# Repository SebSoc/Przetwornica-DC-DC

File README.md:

# Przetwornica-DC-DC
Do budowy przetwornicy zastosowano specjalizowany sterownik MC34063. W tym układzie znajduje się generator impulsów o regulowanym współczynniku wypełnienia, komparator, źródło napięcia odniesienia z kompensacją temperaturową i stopień mocy z kontrolą prądu. Układ składa się z dwóch konfiguracji: przetwornica podwyższająca napięcie - step-up converter oraz przetwornica dostarczająca napięcia ujemne względem napięcia zasilającego - voltage inverting converter. Dzięki zastosowaniu tych dwóch konfiguracji można uzyskać napięcie symetryczne na wyjściu. Kondensatory C1 i C5 filtrują napięcie zasilania, rezystory R1 i R2 oraz analogicznie R5 i R6 połączone równolegle mają wypadkową oporność 0,5 Ω i są wykorzystywane jako obwód kontroli prądu. Kondensatory C3, C4 i dławik L2 oraz analogicznie C7, C8 i L4 filtrują napięcie wyjściowe, potencjometry R4 i R7 umożliwiają regulację tego napięcia. Pojemność C2 i C6 ustalają częstotliwość pracy. Elementy L1, D1 oraz L3, D2 są niezbędne do działania przetwornicy i to od nich głównie zależy jaką funkcję pełni układ.

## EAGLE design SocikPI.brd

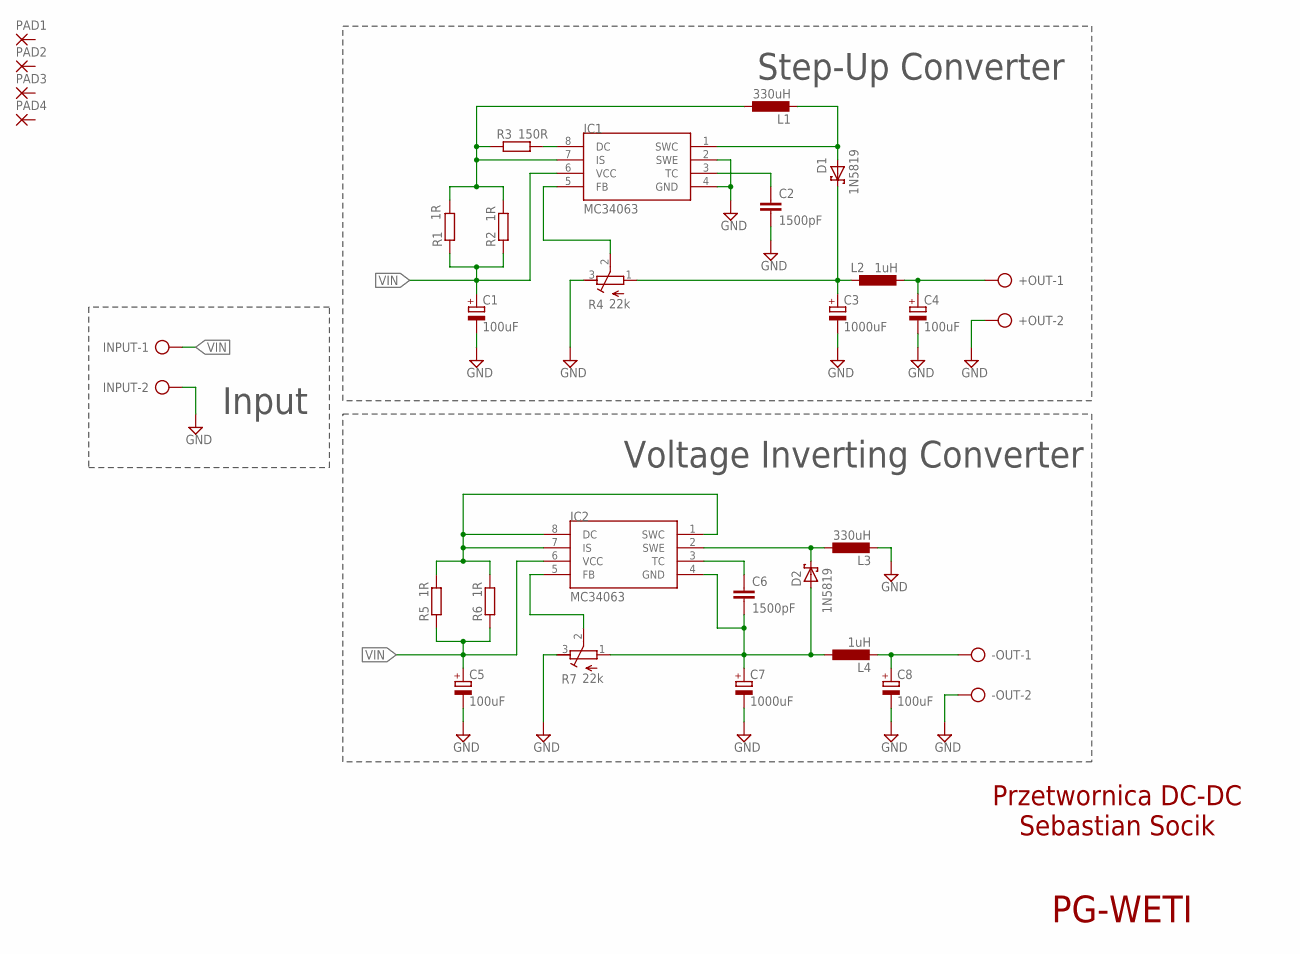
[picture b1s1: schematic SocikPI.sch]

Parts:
+OUT: CON-PTR500_AK500/2
-OUT: CON-PTR500_AK500/2
C1, C4, C5, C8: 100uF; RCL_E2,5-7
C2, C6: 1500pF; C1206
C3, C7: 1000uF; RCL_E5-10,5
D1, D2: 1N5819; DIODE_DO41-7.6
IC1, IC2: MC34063; MC34063_DIL08
INPUT: CON-PTR500_AK500/2
L1, L3: 330uH; RCL_0207/10
L2, L4: 1uH; RCL_0207/10
PAD1, PAD2, PAD3, PAD4: 2,54/1,1
R1, R2, R5, R6: 1R; R1206
R3: 150R; R1206
R4, R7: 22k; PRZETWORNICAL_RTRIMCT32

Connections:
GND: +OUT.2, -OUT.2, C1.-, C2.2, C3.-, C4.-, C5.-, C7.-, C8.-, IC1.2 (SWE), IC1.4 (GND), INPUT.2, L3.2, R4.3 (E), R7.3 (E)
unnamed: C2.1, IC1.3 (TC)
unnamed: IC1.8 (DC), R3.2
unnamed: IC1.7 (IS), L1.1, R1.2, R2.2, R3.1
unnamed: D1.A, IC1.1 (SWC), L1.2
unnamed: IC1.5 (FB), R4.2 (S)
unnamed: C3.+, D1.C, L2.1, R4.1 (A)
unnamed: +OUT.1, C4.+, L2.2
unnamed: IC2.1 (SWC), IC2.7 (IS), IC2.8 (DC), R5.2, R6.2
unnamed: C6.1, IC2.3 (TC)
unnamed: C6.2, C7.+, D2.A, IC2.4 (GND), L4.1, R7.1 (A)
unnamed: IC2.5 (FB), R7.2 (S)
unnamed: -OUT.1, C8.+, L4.2
unnamed: D2.C, IC2.2 (SWE), L3.1
VIN: C1.+, C5.+, IC1.6 (VCC), IC2.6 (VCC), INPUT.1, R1.1, R2.1, R5.1, R6.1

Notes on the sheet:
Step-Up Converter
Voltage Inverting Converter
Przetwornica DC-DC Sebastian Socik
Input
PG-WETI

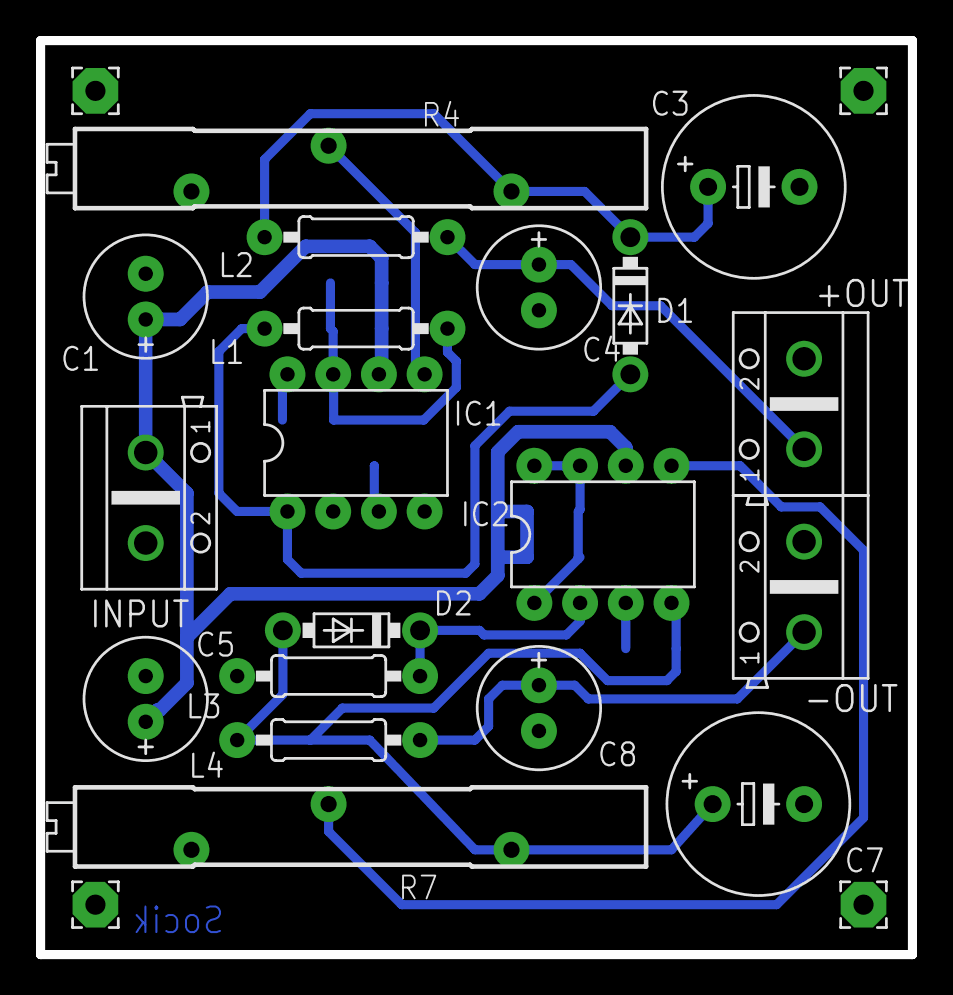
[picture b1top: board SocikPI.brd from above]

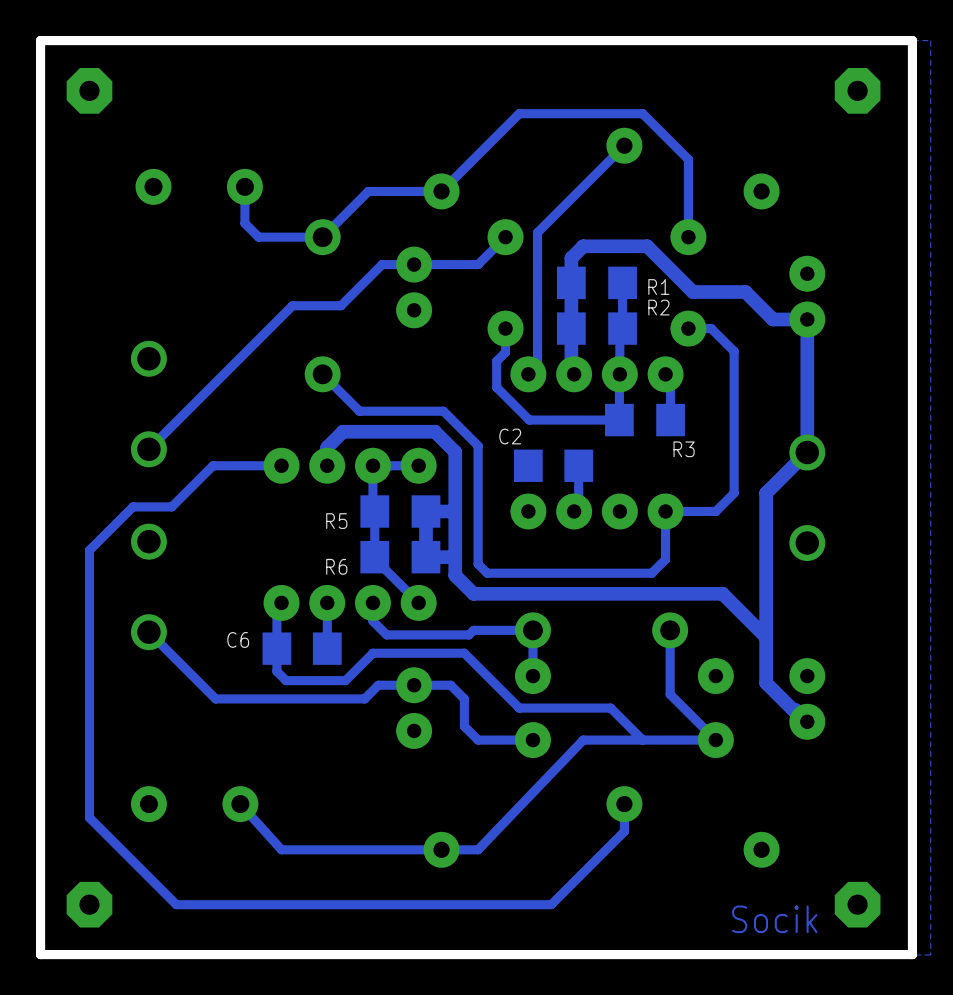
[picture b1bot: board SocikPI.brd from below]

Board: 2 copper layers, 48.4 x 50.8 mm, 30 parts (7 on the bottom side), 15 nets.
